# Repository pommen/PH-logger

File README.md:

# PH-logger
Low power PH logger based on atlas ph logging kit and arduino pro micro

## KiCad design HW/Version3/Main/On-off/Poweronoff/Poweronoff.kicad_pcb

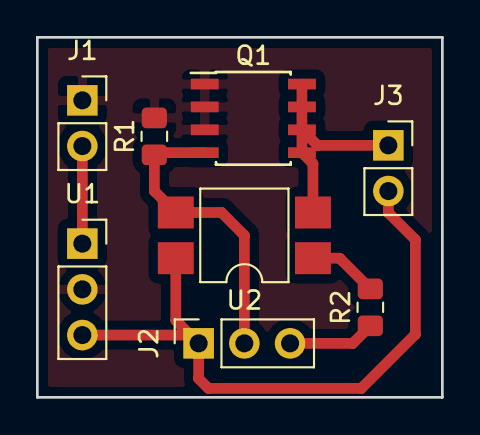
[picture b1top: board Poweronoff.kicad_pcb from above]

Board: 2 copper layers, 22.5 x 20.0 mm, 8 parts (0 on the bottom side), 7 nets.

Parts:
J1: BATT_IN; PinSocket_1x02_P2.54mm_Vertical
J2: Interface; PinSocket_1x03_P2.54mm_Vertical
J3: MCU; PinSocket_1x02_P2.54mm_Vertical
Q1: SI4466; SOIC-8_3.9x4.9mm_P1.27mm
R1: 4k7; R_0805_2012Metric_Pad1.15x1.40mm_HandSolder
R2: 100R; R_0805_2012Metric_Pad1.15x1.40mm_HandSolder
U1: 3-pin-BoostConv; PinSocket_1x03_P2.54mm_Vertical
U2: PC817; SMDIP-4_W7.62mm

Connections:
GND: J1.1, Q1.1, Q1.2, Q1.3, R1.2, U1.2
unnamed: J1.2, U1.1
unnamed: J2.3, R2.1
unnamed: R2.2, U2.1
VCC: J2.1, J3.2, U1.3, U2.4
gate: J2.2, Q1.4, R1.1, U2.3
mcuGND: J3.1, Q1.5, Q1.6, Q1.7, Q1.8, U2.2

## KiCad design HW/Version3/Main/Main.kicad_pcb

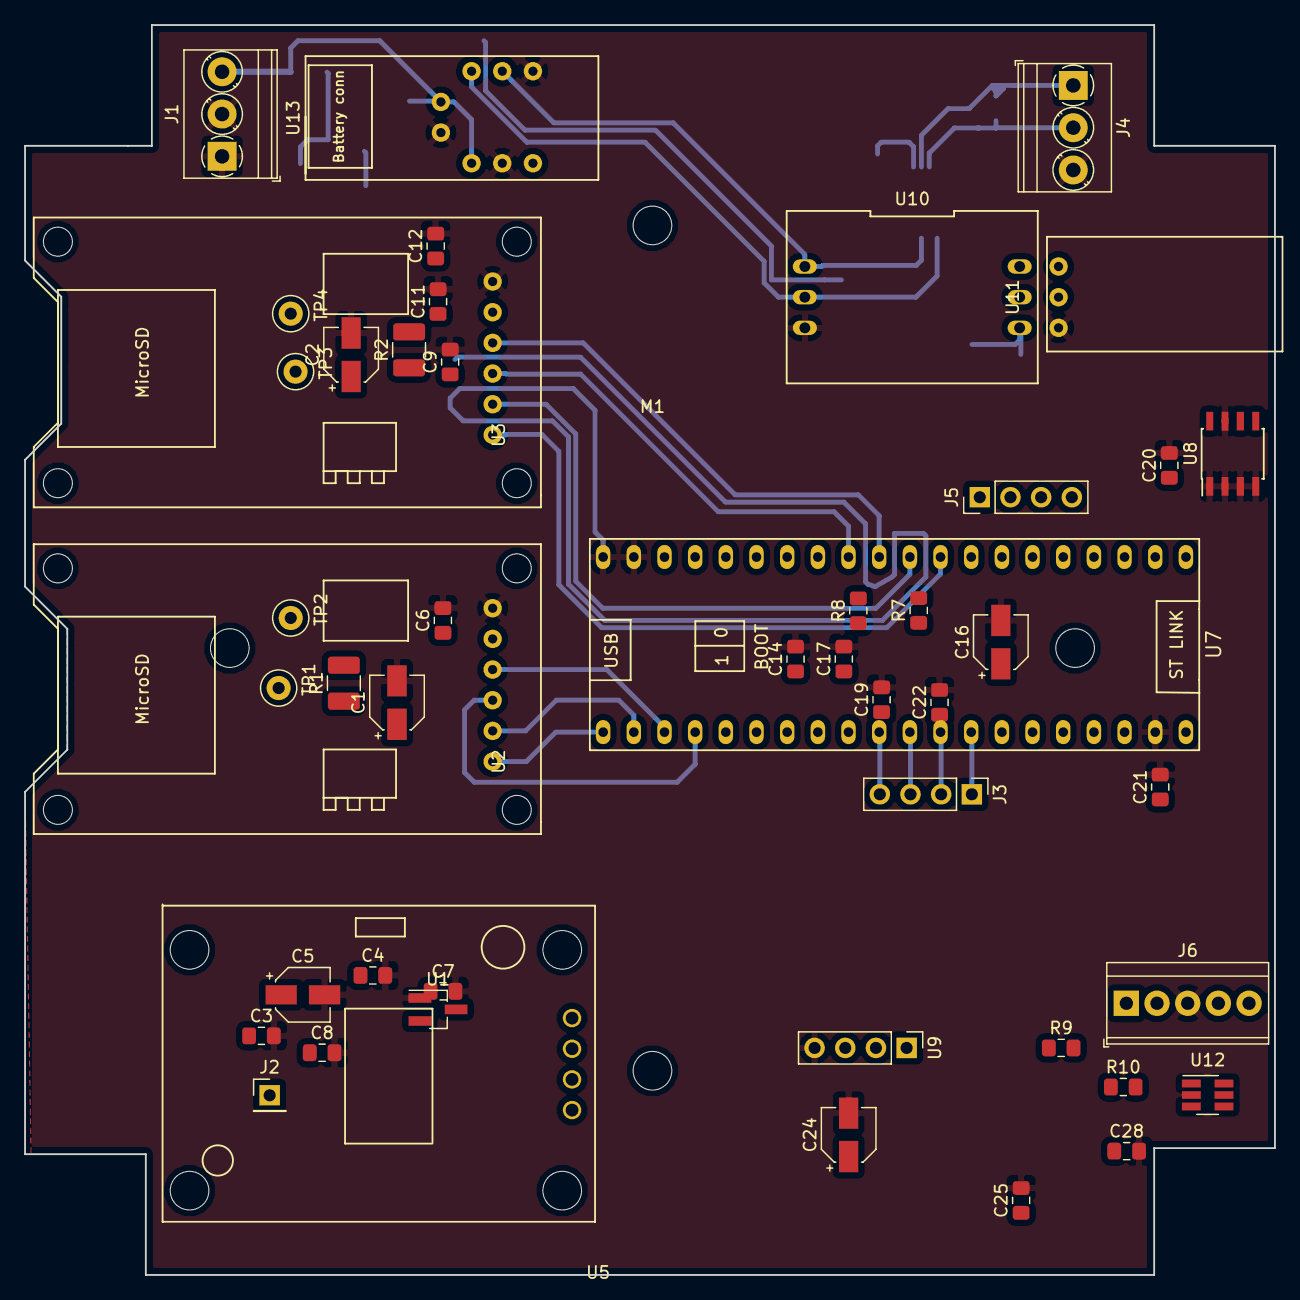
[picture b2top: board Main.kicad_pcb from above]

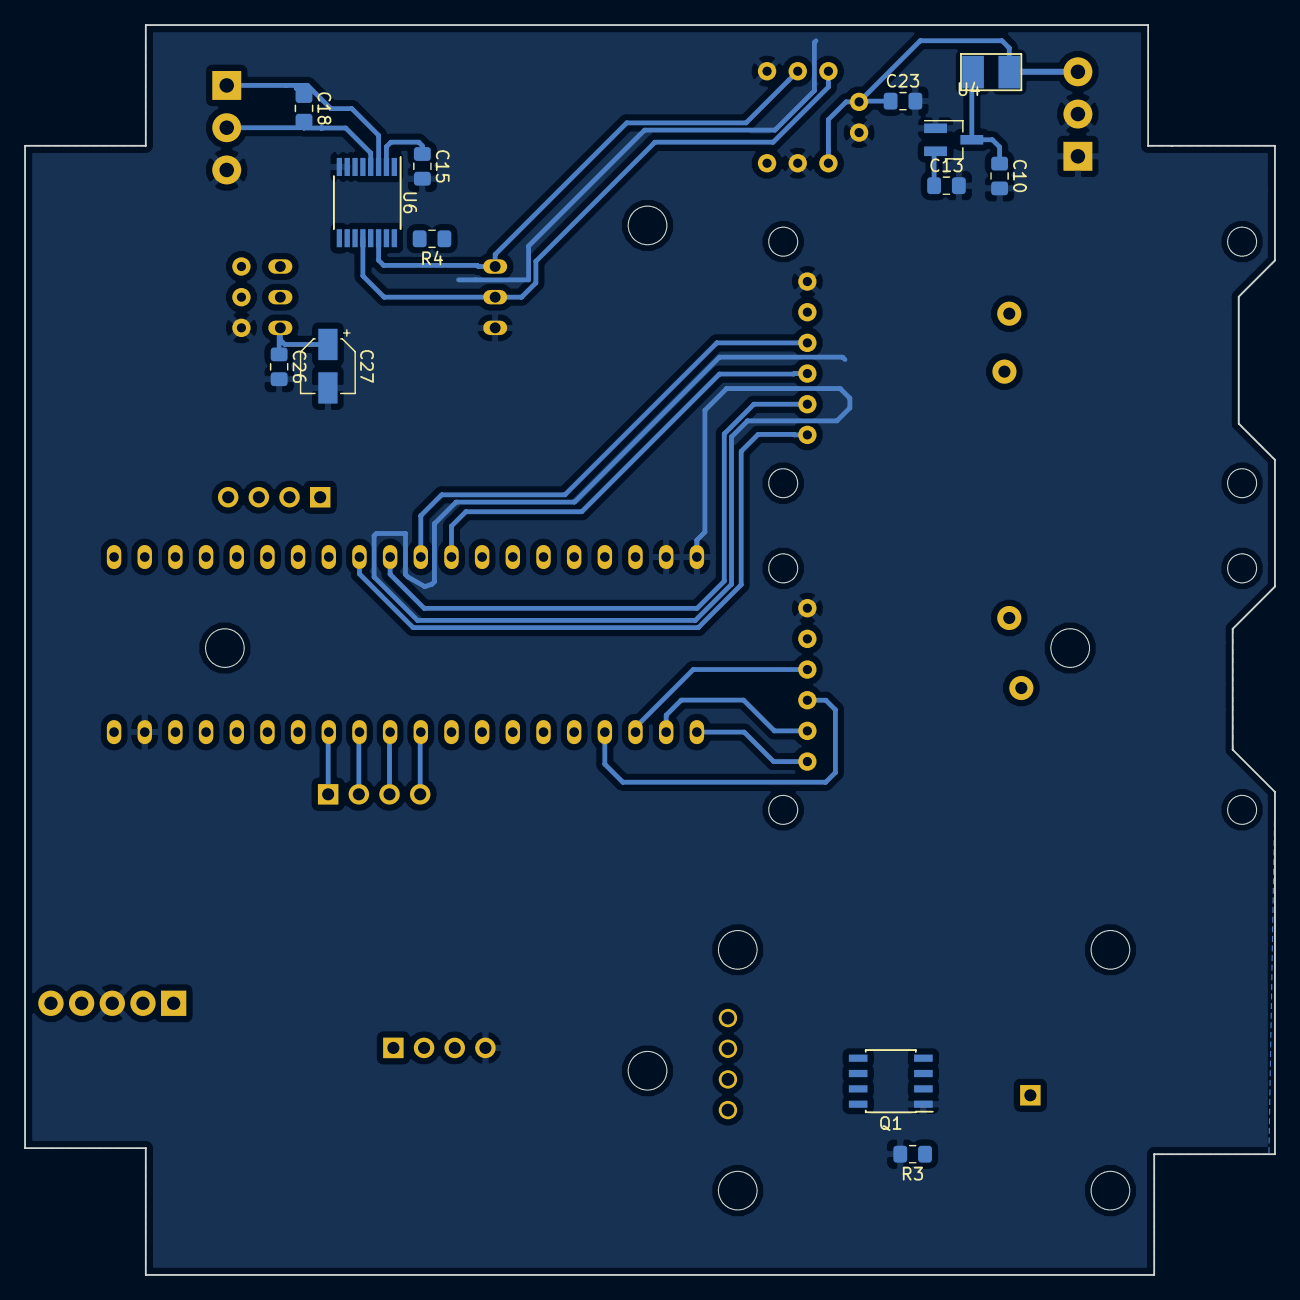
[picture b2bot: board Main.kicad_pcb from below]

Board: 2 copper layers, 103.5 x 103.5 mm, 62 parts (13 on the bottom side), 40 nets.

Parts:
C1, C2, C5, C16, C24, C27: 10u; CP_Elec_4x5.3
C3, C4, C10, C13: 1u; C_0805_2012Metric_Pad1.15x1.40mm_HandSolder
C6, C7, C8, C9, C11, C12, C14, C15, C17, C19, C20, C21, C22, C23, C25, C26, C28: 100n; C_0805_2012Metric_Pad1.15x1.40mm_HandSolder
C18: 680p; C_0805_2012Metric_Pad1.15x1.40mm_HandSolder
F1: Polyfuse; LittleFuse_110F_24V
J1: V_Batt_in; TerminalBlock_Phoenix_PT-1,5-3-3.5-H_1x03_P3.50mm_Horizontal
J2: Vbat; PinHeader_1x01_P2.54mm_Vertical
J3, J5: Spare; PinHeader_1x04_P2.54mm_Vertical
J4: Ext temp; TerminalBlock_Phoenix_PT-1,5-3-3.5-H_1x03_P3.50mm_Horizontal
J6: ExtSw; TerminalBlock_TE_282834-5_1x05_P2.54mm_Horizontal
M1: BOX_Biltema_70x70_IP67; Box_Biltema_70x70mm_IP67
Q1: IRF7341; SOIC-8_3.9x4.9mm_P1.27mm
R1, R2: 0R1; R_1210_3225Metric_Pad1.42x2.65mm_HandSolder
R3: 4K7; R_0805_2012Metric_Pad1.15x1.40mm_HandSolder
R4, R9, R10: 82K; R_0805_2012Metric_Pad1.15x1.40mm_HandSolder
R7, R8: R; R_0805_2012Metric_Pad1.15x1.40mm_HandSolder
TP1, TP2, TP3, TP4: Test_Point; TestPoint_Loop_D1.80mm_Drill1.0mm_Beaded
U1, U4: XC6206P332MR; SOT-23_Handsoldering
U2, U3: SdmicroBreakout; MicroSD_Card_Breakout_Horizontal
U5: GY-NEO6MV2; GY-NEO6MV2 GPS Module
U6: ADM1023; TSSOP-16_4.4x5mm_P0.65mm
U7: Bluepill
U8: AT24CS32-SSHM; SOIC-8_3.9x4.9mm_P1.27mm
U9: OLED_128x32_i2c; PinHeader_1x04_P2.54mm_Vertical
U10: EZ_PH; atlas-scientific.ezo.ph
U11: EZO_BNC
U12: SN74LVC2G14; SOT-23-6_Handsoldering
U13: MAX17043Breakout; MAX17043-Breakout

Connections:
+BATT: C3.1, C7.1, C10.1, C21.1, F1.1, J2.1, U1.3, U4.3, U7.1
ADMStby: R4.2, U6.15, U7.37
Btn: U7.36, U12.4
GND: C1.2, C2.2, C3.2, C4.2, C5.2, C6.2, C7.2, C8.2, C9.2, C10.2, C11.2, C12.2, C13.2, C14.2, C15.2, C16.2, C17.2, C19.2, C20.2, C21.2, C22.2, C23.2, C24.2, C25.2, C26.2, C27.2, C28.2, J1.1, J1.2, J4.3, J6.3, Q1.1, R3.2, U1.1, U2.6, U3.6, U4.1, U6.6, U6.7, U6.8, U6.10, U7.19, U7.20, U7.39, U8.1, U8.2, U8.3, U8.4, U8.7, U9.4, U10.3, U11.1, U12.2, U13.2, U13.4, U13.8
GPS-TX: U5.2, U7.16
GPS_ON: Q1.2, R3.1, U7.14
LogginTypeSw: U7.26, U12.6
MISO1: U3.4, U7.11
MISO2: U2.4, U7.23
MOSI1: U3.3, U7.12
MOSI2: U2.3, U7.24
unnamed: C4.1, C5.1, C8.1, U1.2, U5.4
unnamed: C6.1, C11.1, R1.2, TP1.1, U2.5
unnamed: C9.1, C12.1, R2.2, TP2.1, U3.5
unnamed: C18.1, J4.1, U6.3
unnamed: C18.2, J4.2, U6.4
unnamed: C23.1, F1.2, J1.3, U13.1, U13.7
unnamed: J3.1, U7.33
unnamed: J3.2, U7.32
unnamed: J3.3, U7.31
unnamed: J3.4, U7.30
unnamed: J5.1, U7.8
unnamed: J5.2, U7.7
unnamed: J5.3, U7.6
unnamed: J5.4, U7.5
unnamed: J6.1, U12.3
unnamed: J6.2, R10.2
unnamed: J6.4, U12.1
unnamed: J6.5, R9.2
unnamed: Q1.7, Q1.8, U5.1
unnamed: U6.1, U6.5, U6.9, U6.13, U6.16
unnamed: U10.5, U11.2
unnamed: U10.6, U11.3
SCK1: U3.2, U7.10
SCK2: U2.2, U7.22
SCL: R7.2, U6.14, U7.34, U8.6, U9.2, U10.1, U13.5
SDA: R8.2, U6.12, U7.35, U8.5, U9.1, U10.2, U13.6
SS1: U3.1, U7.9
SS2: U2.1, U7.21
VCC: C1.1, C2.1, C13.1, C14.1, C15.1, C16.1, C17.1, C19.1, C20.1, C22.1, C24.1, C25.1, C26.1, C27.1, C28.1, R1.1, R2.1, R4.1, R7.1, R8.1, R9.1, R10.1, TP3.1, TP4.1, U4.2, U6.2, U7.18, U7.40, U8.8, U9.3, U10.4, U12.5

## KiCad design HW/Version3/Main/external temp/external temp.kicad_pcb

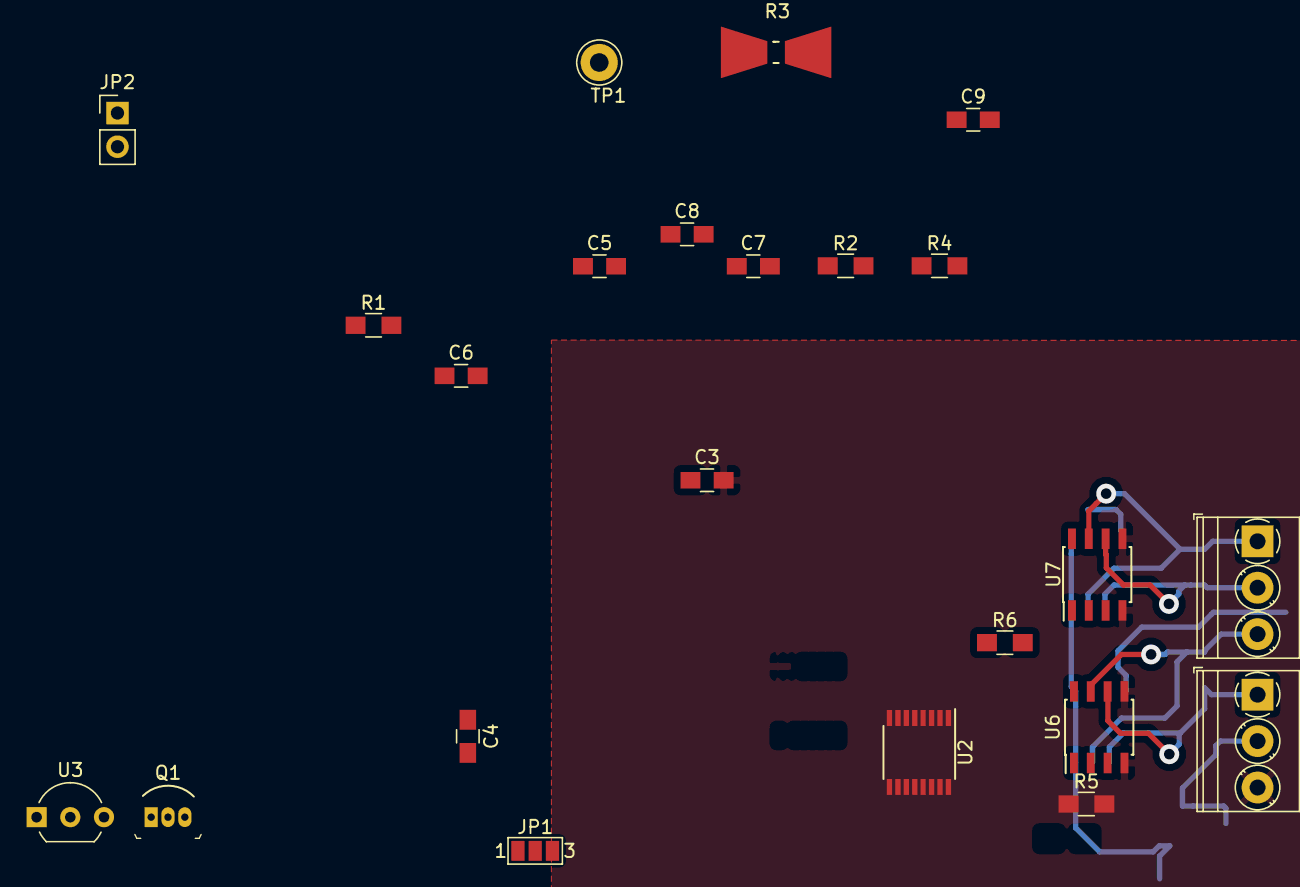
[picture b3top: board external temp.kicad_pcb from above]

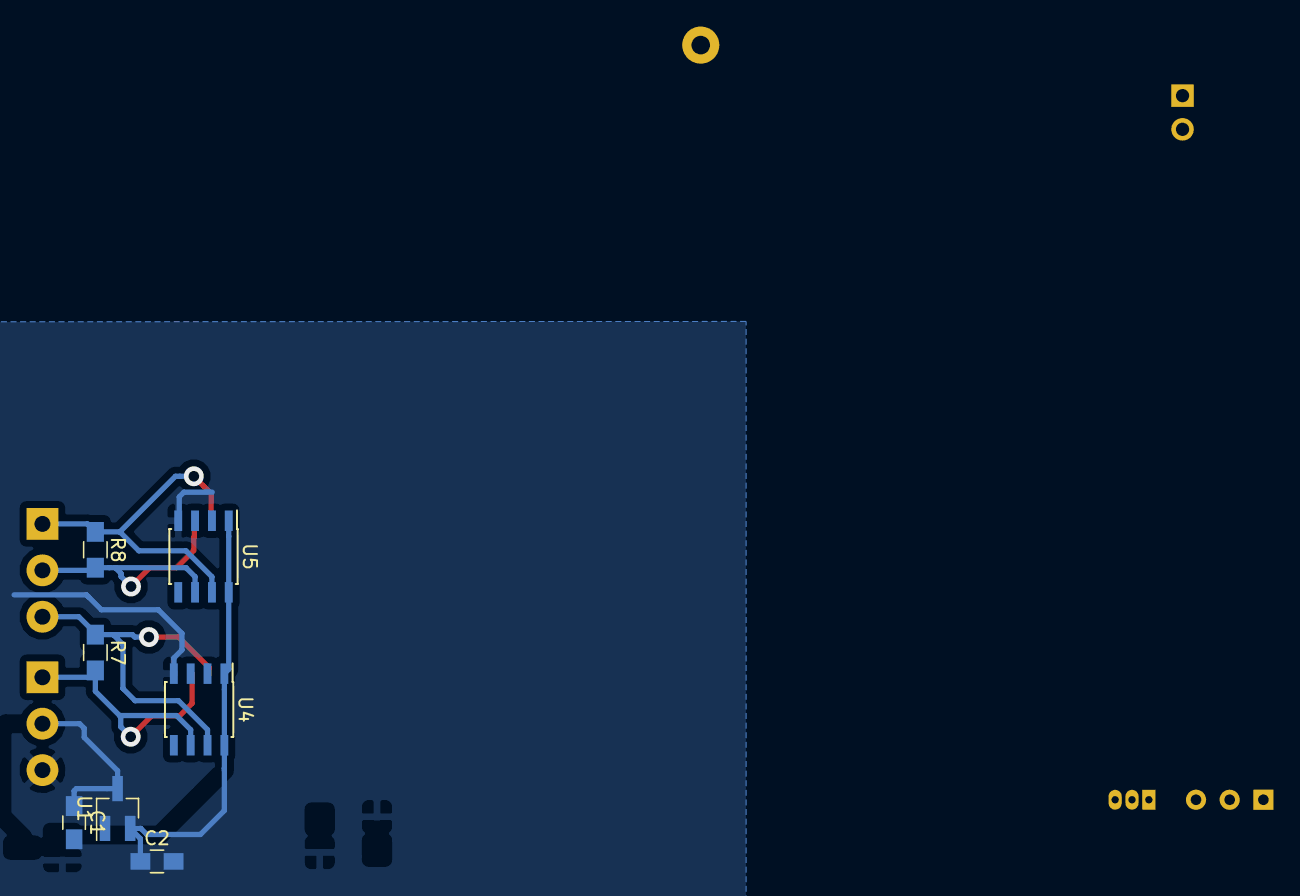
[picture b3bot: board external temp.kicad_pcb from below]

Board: 2 copper layers, 30 parts (7 on the bottom side), 18 nets.

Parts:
C1, C2: 1u; C_0805_HandSoldering
C3, C5, C6, C7, C8, C9: 100n; C_0805_HandSoldering
C4: 1000pF; C_0805_HandSoldering
J1, J2: Screw_Terminal_01x03; TerminalBlock_Phoenix_PT-1,5-3-3.5-H_1x03_P3.50mm_Horizontal
JP1: StandbyTest; SolderJumper-3_P1.3mm_Open_Pad1.0x1.5mm_NumberLabels
JP2: Jumper; PinHeader_1x02_P2.54mm_Vertical
Q1: 2N3904; TO-92-3
R1, R2: 10K; R_0805_HandSoldering
R3: 0R1; Resistor_SMDuniversal_0805to2512_HandSoldering
R4: 4k7; R_0805_HandSoldering
R5, R6: 0R; R_0805_HandSoldering
R7, R8: 54R; R_0805_HandSoldering
TP1: ALRT; TestPoint_Loop_D2.60mm_Drill1.4mm_Beaded
U1: XC6206P332MR; SOT-23_Handsoldering
U2: ADM1023; SSOP-16_3.9x4.9mm_Pitch0.635mm
U3: DS18B20; TO-92_Inline_Wide
U4, U5, U6, U7: DS92LV010A; SOIC-8_3.9x4.9mm_Pitch1.27mm

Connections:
GND: C1.2, C2.2, C3.2, C5.2, C6.2, C7.2, C8.2, C9.2, J2.3, JP1.1, U1.1, U2.6, U2.7, U2.8, U2.10, U3.1, U4.4, U5.4, U6.4, U6.5, U7.4, U7.5
unnamed: C4.1, Q1.2, Q1.3, U2.3
unnamed: C4.2, Q1.1, U2.4
unnamed: JP1.2, U2.15
unnamed: JP2.2, R4.2, U3.2
unnamed: R3.2, U2.2
unnamed: R5.2, U6.3
unnamed: R6.2, U7.3
unnamed: TP1.1, U2.11
unnamed: U2.1, U2.5, U2.9, U2.13, U2.16
SCK: R2.2, R5.1, U2.14, U4.2
SCK+: J1.3, R7.1, U4.7, U6.7
SCL-: J2.1, R7.2, U4.6, U6.6
SDA: JP2.1, R1.2, R6.1, U2.12, U5.2
SDA+: J1.1, R8.1, U5.7, U7.7
SDA-: J1.2, R8.2, U5.6, U7.6
VCC: C2.1, C3.1, C5.1, C6.1, C7.1, C8.1, C9.1, JP1.3, R1.1, R2.1, R3.1, R4.1, U1.2, U3.3, U4.1, U4.8, U5.1, U5.8, U6.8, U7.8
VIN: C1.1, J2.2, U1.3

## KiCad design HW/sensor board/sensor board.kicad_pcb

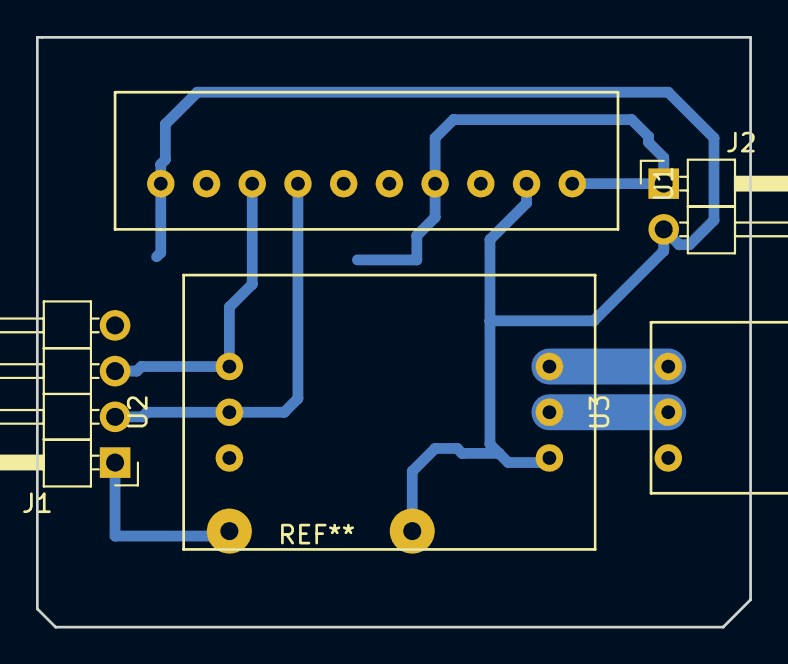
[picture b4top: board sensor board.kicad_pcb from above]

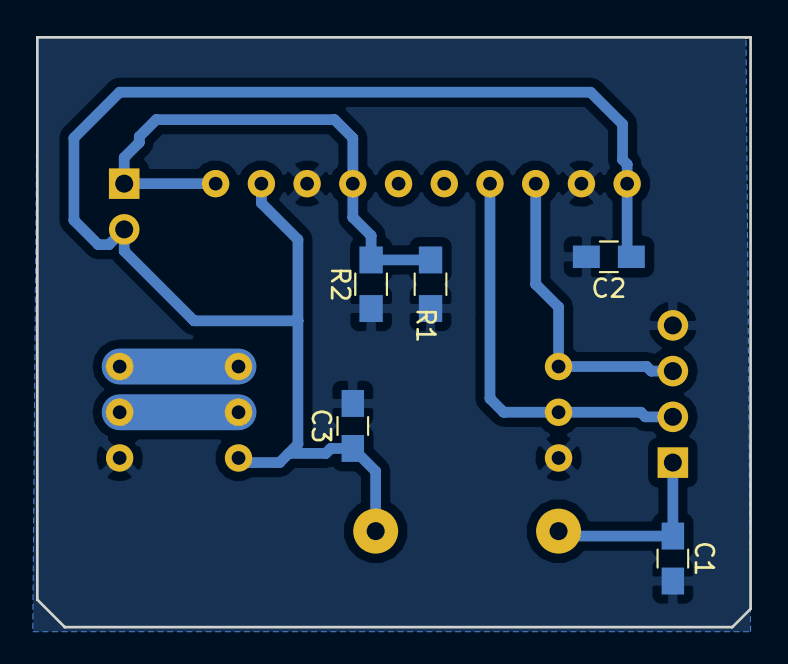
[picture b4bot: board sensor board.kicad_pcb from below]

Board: 2 copper layers, 39.6 x 32.8 mm, 10 parts (5 on the bottom side), 7 nets.

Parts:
C1, C2, C3: C_Small; C_0805_HandSoldering
J1: CONN_01X04_MALE; Pin_Header_Angled_1x04_Pitch2.54mm
J2: CONN_01X02_MALE; Pin_Header_Angled_1x02_Pitch2.54mm
R1: 20k; R_0805_HandSoldering
R2: 20K; R_0805_HandSoldering
U1: ads1115; ADS1115
U2: EZO_PH
U3: EZO_BNC

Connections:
GND: C1.2, C2.2, C3.2, J1.4, R1.1, R2.1, U1.2, U1.8, U2.6, U3.3
unnamed: J2.1, R1.2, R2.2, U1.7, U1.10
unnamed: U2.2, U3.2
unnamed: U2.3, U3.1
SCL: J1.3, U1.3, U2.4
SDA: J1.2, U1.4, U2.5
VCC: C1.1, C2.1, C3.1, J1.1, J2.2, U1.1, U1.9, U2.1

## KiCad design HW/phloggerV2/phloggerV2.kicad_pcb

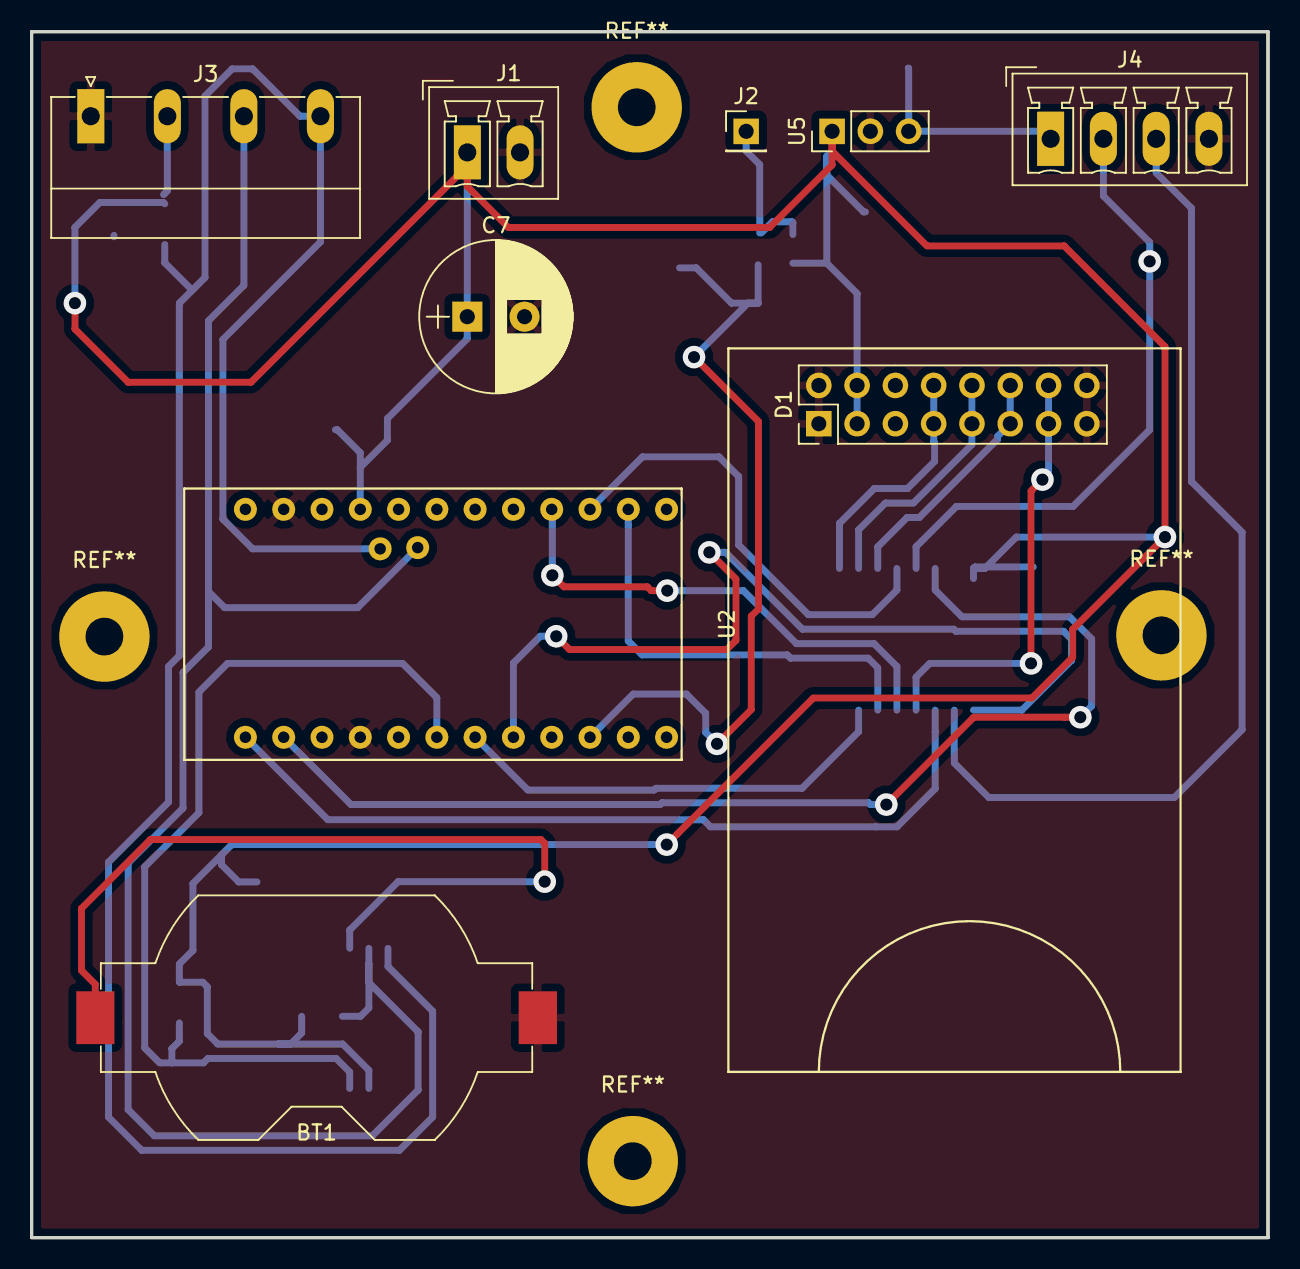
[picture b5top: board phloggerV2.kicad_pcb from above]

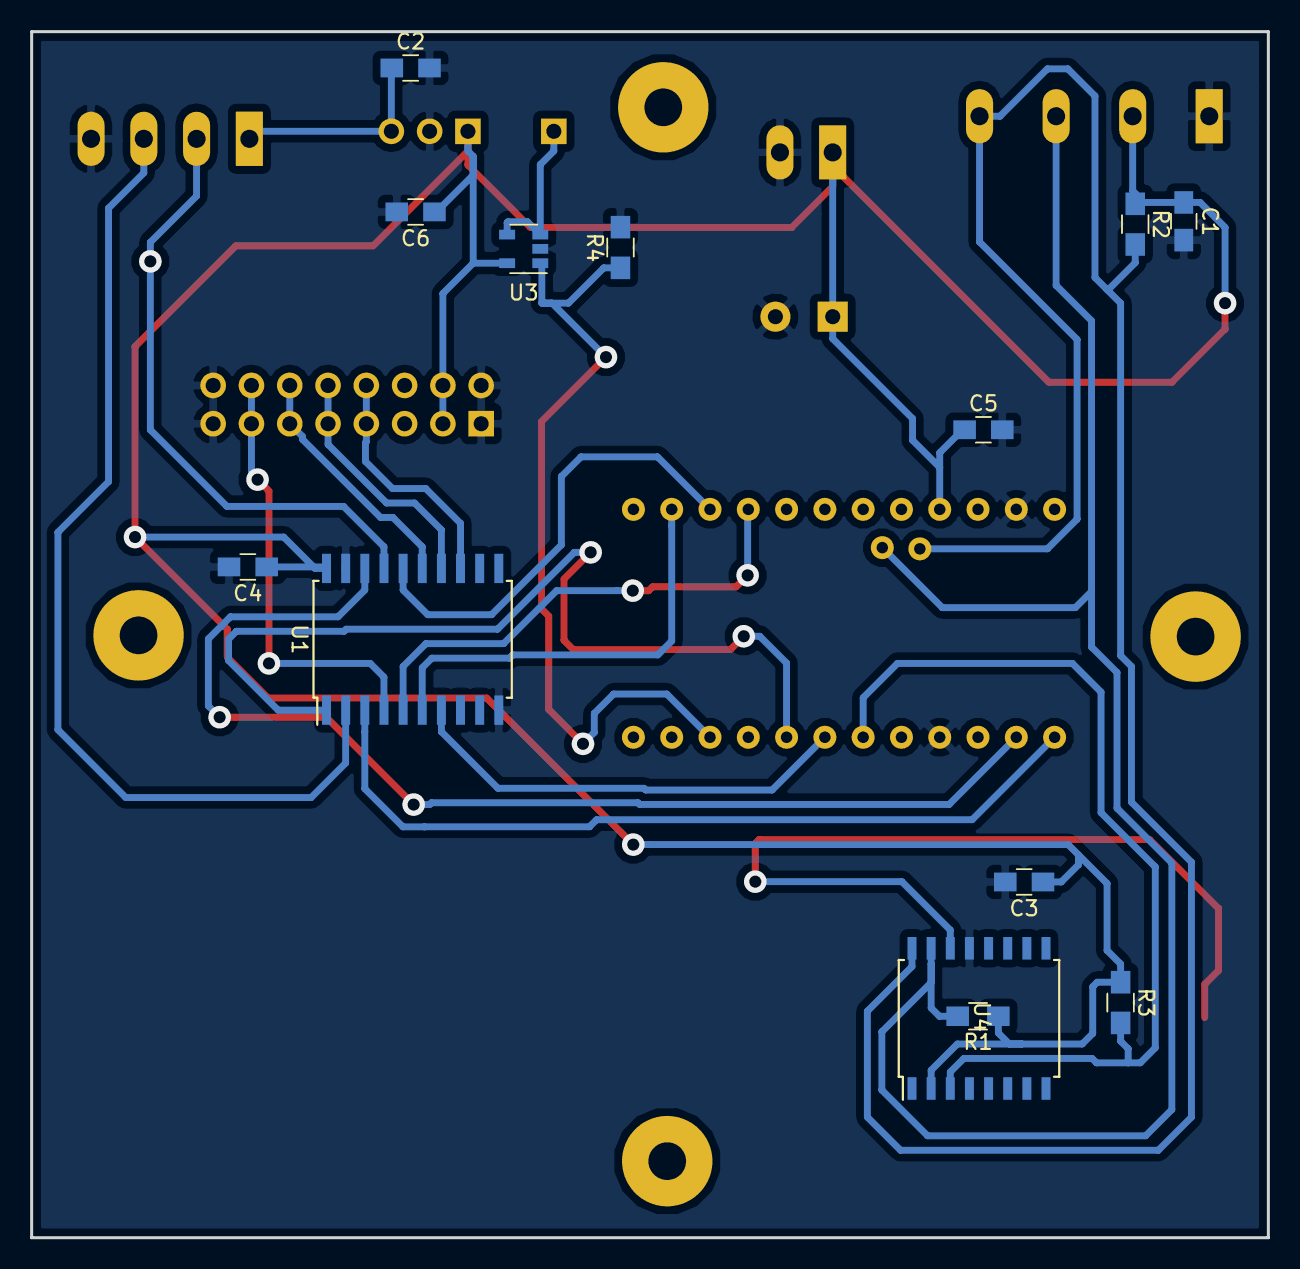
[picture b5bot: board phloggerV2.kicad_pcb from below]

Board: 2 copper layers, 82.0 x 80.0 mm, 22 parts (13 on the bottom side), 22 nets.

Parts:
BT1: Battery_Cell; Keystone_1058_1x2032-CoinCell
C1, C2: 1u; C_0805_HandSoldering
C3, C4, C5, C6: 0,1u; C_0805_HandSoldering
C7: 220u; CP_Radial_D10.0mm_P3.80mm
D1: SD-BREAKOUT; SD-breakout
J1: BATTERI CON; PhoenixContact_MCV-G_02x3.50mm_Vertical
J2: boost_conv_ena; Pin_Header_Straight_1x01_Pitch2.54mm
J3: PH_PROBE; PhoenixContact_MC-G_04x5.08mm_Angled
J4: GPS; PhoenixContact_MCV-G_04x3.50mm_Vertical
R1, R2: 4k7; R_0805_HandSoldering
R3: 10K; R_0805_HandSoldering
R4: 10k; R_0805_HandSoldering
U1: 74HCT541; SOIC-20W_7.5x12.8mm_Pitch1.27mm
U2: pro-mini-deek; Pro-mini-deek-noheaders
U3: LM321; SOT-23-5
U4: DS3231; SOIC-16W_7.5x10.3mm_Pitch1.27mm
U5: 3-pin-BoostConv; Pin_Header_Straight_1x03_Pitch2.54mm

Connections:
GND: BT1.2, C1.2, C2.2, C3.2, C4.2, C5.2, C6.2, C7.2, D1.1, D1.8, D1.9, D1.16, J1.2, J3.1, J4.4, R4.2, U1.10, U1.19, U2.4, U2.25, U3.2, U4.13, U5.2
GPS_ON: R4.1, U2.10, U3.1
INT: R3.2, U2.6, U4.3
MCU_CS: U1.7, U2.7
MCU_MISO: U1.16, U2.15
MCU_MOSI: U1.6, U2.14
MCU_SCK: U1.5, U2.16
unnamed: BT1.1, U4.14
unnamed: C2.1, J4.1, U5.3
unnamed: J2.1, U3.3, U3.4
RX_UART: J4.2, U1.17
RX_UART_MCU: U1.3, U2.1
SCL: J3.4, R2.2, U2.22, U4.16
SDA: J3.3, R1.2, U2.21, U4.15
SD_CS: D1.4, D1.13, U1.13
SD_MISO: D1.7, D1.10, U1.4
SD_MOSI: D1.5, D1.12, U1.14
SD_ON: U1.1, U2.8
SD_SCK: D1.6, D1.11, U1.15
TX_UART: J4.3, U1.2
TX_UART_MCU: U1.18, U2.2
VCC: C1.1, C3.1, C4.1, C5.1, C6.1, C7.1, D1.2, D1.15, J1.1, J3.2, R1.1, R2.1, R3.1, U1.20, U2.23, U3.5, U4.2, U5.1

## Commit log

2017-08-08 First working realise
2017-08-08 bug fixes with GPS
2017-08-08 Added kicad files
2018-06-09 kicad 5
2018-06-15 STM32 ph test first commit
2018-06-15 stm32
2018-06-17 Sync GPS time to RTC
2018-06-17 better sleepmode
2018-06-17 sunday tinkering
2018-06-21 Better logging + better date
2018-06-26 board
2018-07-15 Layout beginning
2018-07-19 Before
2018-07-19 Bore we start finalizing
2018-07-30 Finnmarks version
2018-07-31 v3 hw
2019-03-14 V4 started
2019-03-19 V4 beginning
2019-04-26 2019 mod
